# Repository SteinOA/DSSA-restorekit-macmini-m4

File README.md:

# DSSA – Mac mini M4 gjenopprettet fra Windows

**Vellykket gjenoppretting uten en ekstra Mac.** Dette repoet dokumenterer hvordan en Mac mini M4 (2024, Mac16,10) med en ny, tom 2 TB SSD ble gjenopprettet fra en Windows x64-PC. Mac-en startet deretter i macOS-oppsettsassistenten, og oppstarten ble bekreftet med bilder.

Forsøk 9 fullførte gjenopprettingen av macOS 15.6.1 (24G90) med avslutningskode 0. Her er kildekoden, de lokale rettelsene og resultatene fra arbeidet samlet.

Resultatet gjelder den konkrete maskinen og programversjonen som ble brukt. Den arkiverte programversjonen er låst til denne enhetens identitet; andre Mac-maskiner er ikke verifisert av DSSA. Arkivet inneholder enhetsspesifikke opplysninger fra forsøket.

**Sikkerhetsgjennomgang gjenstår:** Skanningene fant kjente sårbarhetsvarsler i avhengigheter. Se [faktiske resultater og gjenstående arbeid](docs/SECURITY-REVIEW-2026-10-25.md) før en ny brukerpakke bygges eller deles.

## Slik ble det gjort

Se [den tekniske fremgangsmåten](docs/FREMGANGSMATE.md) for forberedelser, bygging, maskintilpasning, driveroppsett, DFU, overvåket gjenoppretting og opprydding.

For videre arbeid på en utgave som velger målmaskin per kjøring, se også [DSSA-Mac-mini-M4-Restore](https://github.com/SteinOA/DSSA-Mac-mini-M4-Restore). Det repoet inneholder den generaliserte utviklingsutgaven; dette arkivet dokumenterer det fysisk vellykkede forsøket.

## Før Mac-en åpnes: sikkerhetskopi, Aktiveringslås og sletting

**Denne fremgangsmåten er beregnet på å gjenopprette macOS til en tom erstatnings-SSD. Den bevarer ikke data og er ikke et klone- eller dataredningsverktøy. En full DFU-gjenoppretting sletter alle data på SSD-en som er installert i mål-Mac-en. Hvis den gamle SSD-en er installert som mål, slettes også dataene på den. Ta og kontroller sikkerhetskopi før du slår av maskinen og bytter SSD.**

[Leverandørens bruksanvisning](https://expandmacmini.com/pages/diy-guide) advarer om at prosedyren sletter alle data på Mac mini, og at data på den opprinnelige SSD-en vil være utilgjengelige etter byttet og fullført gjenoppretting. Ikke regn med å sette inn den gamle SSD-en igjen som sikkerhetskopi eller for å finne Apple-kontoen etterpå.

Før maskinen åpnes, ber leverandøren eieren kontrollere den nøyaktige e-postadressen til Apple-kontoen og logge ut i Systeminnstillinger. Kontroller selv at du kan logge inn på kontoen. Ikke del passord eller legg dem i repoet.

[Apple forklarer Aktiveringslås og hvordan den slås av](https://support.apple.com/en-ie/102541): Slå av Finn Mac under Systeminnstillinger → navnet ditt → iCloud → Se alle → Finn Mac, og godkjenn selv når du blir bedt om det. Aktiveringslås er noe annet enn FileVault-diskkryptering. Den lenkede leverandørveiledningen sier ikke at FileVault må slås av. SSD-bytte og dette programmet kan ikke omgå Aktiveringslås.

Gjør disse kontrollene før avslåing og demontering.

Se [resultatet](docs/FORSOK9-RESULTAT.txt) og [kontrollpunktene](results/attempt9-restore-result.json). Den konkrete native Windows-portfeilen er rettet og testet før det vellykkede forsøket; [rettelsen er dokumentert her](docs/NATIVE-PORT-RETTELSE.txt).

Etter det vellykkede forsøket ble den midlertidige driverpakken, sertifikattilliten og den private nøkkelen fjernet. Apples drivere og tjeneste ble beholdt, og Windows-beskyttelsen var på. Detaljene er bevart i [arbeidsnotatet fra forsøket](docs/FORTSETT-HER-I-KVELD.txt).

## Innhold i repoet

- `source/`: komplett kildekode fra RestoreKit v0.5.13 med lokale rettelser og innholdet i alle vendor-moduler.
- `archives/source-snapshot.zip`: samme 2 133 kildefiler med nøyaktige opprinnelige byte. Bruk dette arkivet når kontrollsummene i `source-manifest.json` skal sammenlignes; enkelte vendor-moduler har egne Git-regler for linjeskift.
- `patches/`, `provenance.json`, `source-manifest.json`: opprinnelse, endringer, lisenser og kontrollsummer.
- `bin/windows-x64/restorekit.exe`: ferdig Windows-program, SHA256 `B59206BC8E7046FF696A87DF029BD919BCD6659E06E82D11DD940F67126D2F93`.
- `ops/`: klargjorte skript for ett overvåket forsøk og etterfølgende opprydding. De er tilpasset det opprinnelige lokale oppsettet og er ikke generelle installasjonsskript for en ny kloning av repoet.
- `driver/pid1905/`: kun den avgrensede INF/CAT-pakken for siste restore-modus. CAT inneholder det eksisterende offentlige signeringssertifikatet. Ingen privat signeringsnøkkel er bevart eller lastet opp. Historisk signaturkontroll betyr ikke at sertifikatet nå er betrodd på PC-en.
- `results/`: programtesten, oppryddingsbevis og faktiske GitHub Actions-resultater.
- `history/`: eldre skript som dokumentasjon, lagret som tekst; de skal ikke kjøres.

Midlertidige drivere og sertifikattillit krever opprydding etter bruk, også ved feil. Ikke bruk den opprinnelige brede `setup-driver`-kommandoen.

Firmware (IPSW), private nøkler, innloggingsopplysninger og lokale sertifikatlagre inngår ikke i distribusjonen.

## Hva de automatiske testene viser

Identitetsparseren og regresjonstestene er testet på Ubuntu 24.04 med GCC og Clang, inkludert AddressSanitizer og UndefinedBehaviorSanitizer, og på Windows Server 2022 med MSVC. Tre separate testkjøringer bruker ulike deterministiske startverdier og tester 100 000 tilfeller med ugyldige inndata hver.

Dette er programvaretester uten tilgang til USB-enheter, drivere, sertifikatlagre, firmware eller Mac-maskinvare. De kontrollerer parserens oppførsel og minnehåndtering. Den fysiske gjenopprettingen er dokumentert separat i resultatene fra forsøk 9.

`source-provenance.json` inneholder SHA-256-kontrollsummer for den kopierte produksjonsheaderen og de opprinnelige testdataene. Testarbeidsflytene har lesetilgang (`contents: read`), en grense på ti minutter per jobb og bruker ingen repository secrets.

## Diskmåling og ønsket enkel brukerpakke

[Én måleøkt og krav til en veiledet Windows-pakke](docs/STORAGE-TEST-AND-USER-PACKAGE.md) dokumenterer 2 TB-modulen fra Expand Mac mini, resultatene for alle tre disker og testens begrensninger. En enkel nedlastbar brukerpakke med grundig veiledning er et utviklingsmål, ikke en allerede verifisert ettklikksløsning. Andre SSD-moduler er foreløpig ikke testet.

## Sikkerhet og automatiske kontroller

Se [sikkerhetspolicyen](SECURITY.md) for privat rapportering og [kontrollenes omfang og begrensninger](docs/SECURITY-CHECKS.md). Faktiske resultater ligger under [GitHub Actions](https://github.com/SteinOA/DSSA-restorekit-macmini-m4/actions). En konfigurert kontroll er ikke det samme som en bestått kontroll. Avhengighetsoppdateringer foreslås i pull requests; de flettes ikke automatisk inn i dette historiske arkivet.

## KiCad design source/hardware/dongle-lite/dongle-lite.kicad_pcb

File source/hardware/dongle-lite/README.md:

# Dongle-Lite — KiCad hardware

The USB 2.0 variant of the RecoverKit dongle: an RP2354A + FUSB302B board that
forces an Apple Silicon / T2 Mac into DFU over USB-PD, no keyboard dance
required. See [`../README.md`](../README.md) for how the dongle family works
and how the Lite compares to the [Dongle-Pro](../dongle-pro/), `./PRD.md` for
the product spec, and `./BOM-sourcing.md` for parts sourcing.

## How it works (short version)

The host plugs into J1, the target Mac into J2. A CH334F USB 2.0 hub puts two
devices on the host's bus: the RP2354A (control + CDC serial for `restorekit`)
and the target itself. The FUSB302B drives the *target* CC line with Apple's
vendor-defined USB-PD messages to flip the Mac into DFU; an AP22653 load
switch power-cycles target VBUS for clean re-enumeration; two 74AVC1T45s
break out the target's SBU debug UART at 1.2 V. Restore data flows host ↔
target straight through the hub — the MCU only triggers, never proxies.

## Status

- **Schematic:** complete, single sheet, functionally clustered, ERC 0.
- **Layout:** two builds of the same netlist:
  - `dongle-lite.kicad_pcb` — original two-sided 4-layer layout
    (`mfg-jlcpcb/`).
  - `dongle-lite-1s4l.kicad_pcb` — **single-sided** 4-layer relayout for
    JLCPCB Economic PCBA (`mfg-jlcpcb-1s4l/`, DRC report checked in). This is
    the one to order.
- **Firmware:** `../../crates/dongle-lite-fw` (Embassy, `rp235xa`). The GPIO
  map lives in the firmware source and matches `gen/board.py`.

## Clusters

One flat sheet (`dongle-lite.kicad_sch`), five functional clusters — parts
that talk to each other are drawn wired together, only cross-cluster signals
use labels:

| Cluster | Contents |
|---------|----------|
| MCU core | RP2354A (internal stacked flash — no external QSPI part), 12 MHz crystal, BOOT button, Tag-Connect J3 |
| USB-PD | FUSB302B, I²C pull-ups, target CC |
| USB hub + ports | CH334F hub, both 16-pin USB-C receptacles, ESD arrays, host CC pull-downs |
| SBU serial | 2× 74AVC1T45 1.2 V level translators |
| Power | 3.3 V + 1.2 V LDOs, target-VBUS load switch, LEDs |

USB D+/D− pairs are impedance-controlled differential pairs on the PCB.

## How this was built

Every part is a real LCSC component. Symbols, footprints, and 3D models were
pulled with [`easyeda2kicad`](https://github.com/uPesy/easyeda2kicad.py) into
the project-local libraries under `lib/` (shared with the Pro via its `lib`
symlink); `sym-lib-table` / `fp-lib-table` register them via `${KIPRJMOD}`.

The schematic is generated, not hand-drawn: `gen/board.py` is the
authoritative netlist (every part → cluster placement, every pin → net) and
`gen/gen.py` emits the `.kicad_sch`. Regenerate:

```sh
cd hardware/dongle-lite
python3 gen/board.py            # writes dongle-lite.kicad_sch
kicad-cli sch erc dongle-lite.kicad_sch
```

## Key parts (all LCSC)

| Ref | Part | LCSC | Function |
|-----|------|------|----------|
| U1 | RP2354A | C41378174 | MCU (USB-native composite; 2 MB internal flash) |
| U2 | FUSB302BMPX | C132291 | USB-PD PHY, drives target CC (Apple DFU VDM) |
| U3 | CH334F | C5187527 | USB 2.0 hub — host sees MCU + target. `PSELF` (18) and `RESET#/CDP` (16) are left **open** — see below |
| U5 | RT9013-33GB | C47773 | 3.3 V LDO from host 5 V |
| U6 | TLV70212 | C81462 | 1.2 V LDO for the SBU translator low side |
| U8, U9 | 74AVC1T45GW | C282330 | SBU1/SBU2 level translators (3.3 ↔ 1.2 V) |
| U10 | AP22653 | C2158037 | Target-VBUS load switch (current-limited) |
| D10, D11 | USBLC6-2SC6 | C7519 | ESD arrays on host / target D± |
| J1, J2 | HRO TYPE-C-31-M-12 | C165948 | Host / target USB-C (16-pin) |
| Y1, Y2 | 12 MHz 3225 | C9002 | MCU + hub crystals |

Full BOM/CPL for ordering are in the `mfg-jlcpcb*/` packages.

### Hub strap pins

`PSELF` (18) and `RESET#/CDP` (16) on U3 are both left open, matching Adafruit's
CH334F breakout (product 5997).

`PSELF` has a built-in pull-up and defaults high = **self-powered**, which is
what makes the hub advertise 500 mA per downstream port. Tied to GND it
advertises bus-powered and caps every port at one unit load, 100 mA. A target
Mac in DFU fits under that, but every later restore stage asks for 500 mA, so
the host refuses to configure the target and the restore dies partway through
with a power error. The board still draws from the host's VBUS — this is a
declaration, not a supply.

`RESET#/CDP` is sampled at power-up too: held high it enables CDP (downstream
charging-port advertisement) and turns off the hub's low-power sleep. The
datasheet wants it "completely suspended when not reset", so there is no
pull-up on it.

## ERC configuration

`pin_not_driven`, `pin_to_pin`, `lib_symbol_issues`, and `lib_symbol_mismatch`
are set to *ignore* in the project files: the LCSC-generated symbols type
passive/IO pins as "Input/Unspecified", not real disconnections. Everything
else keeps default severity.

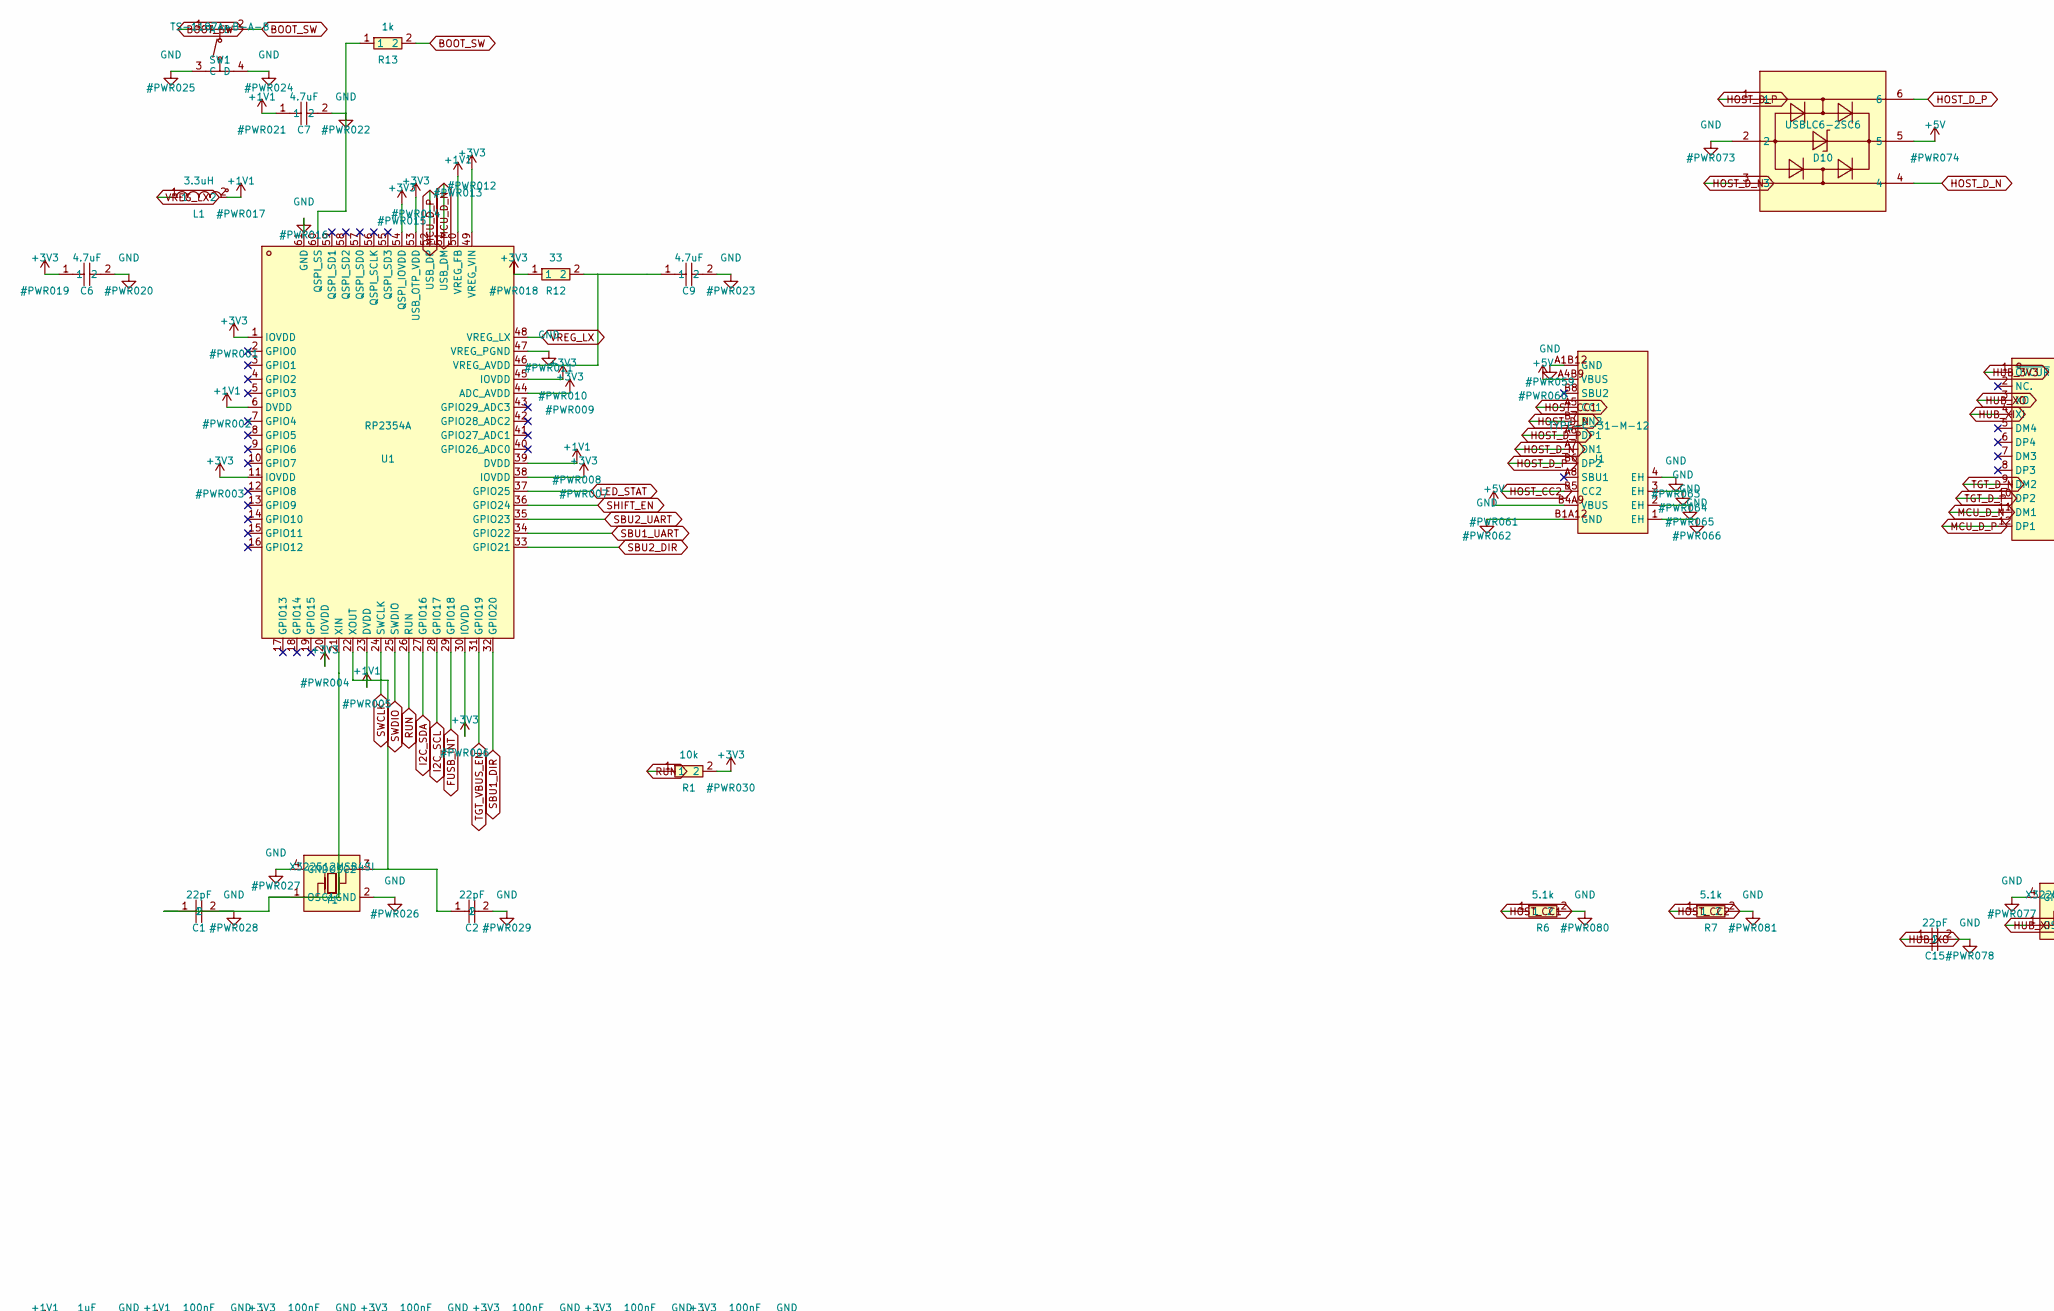
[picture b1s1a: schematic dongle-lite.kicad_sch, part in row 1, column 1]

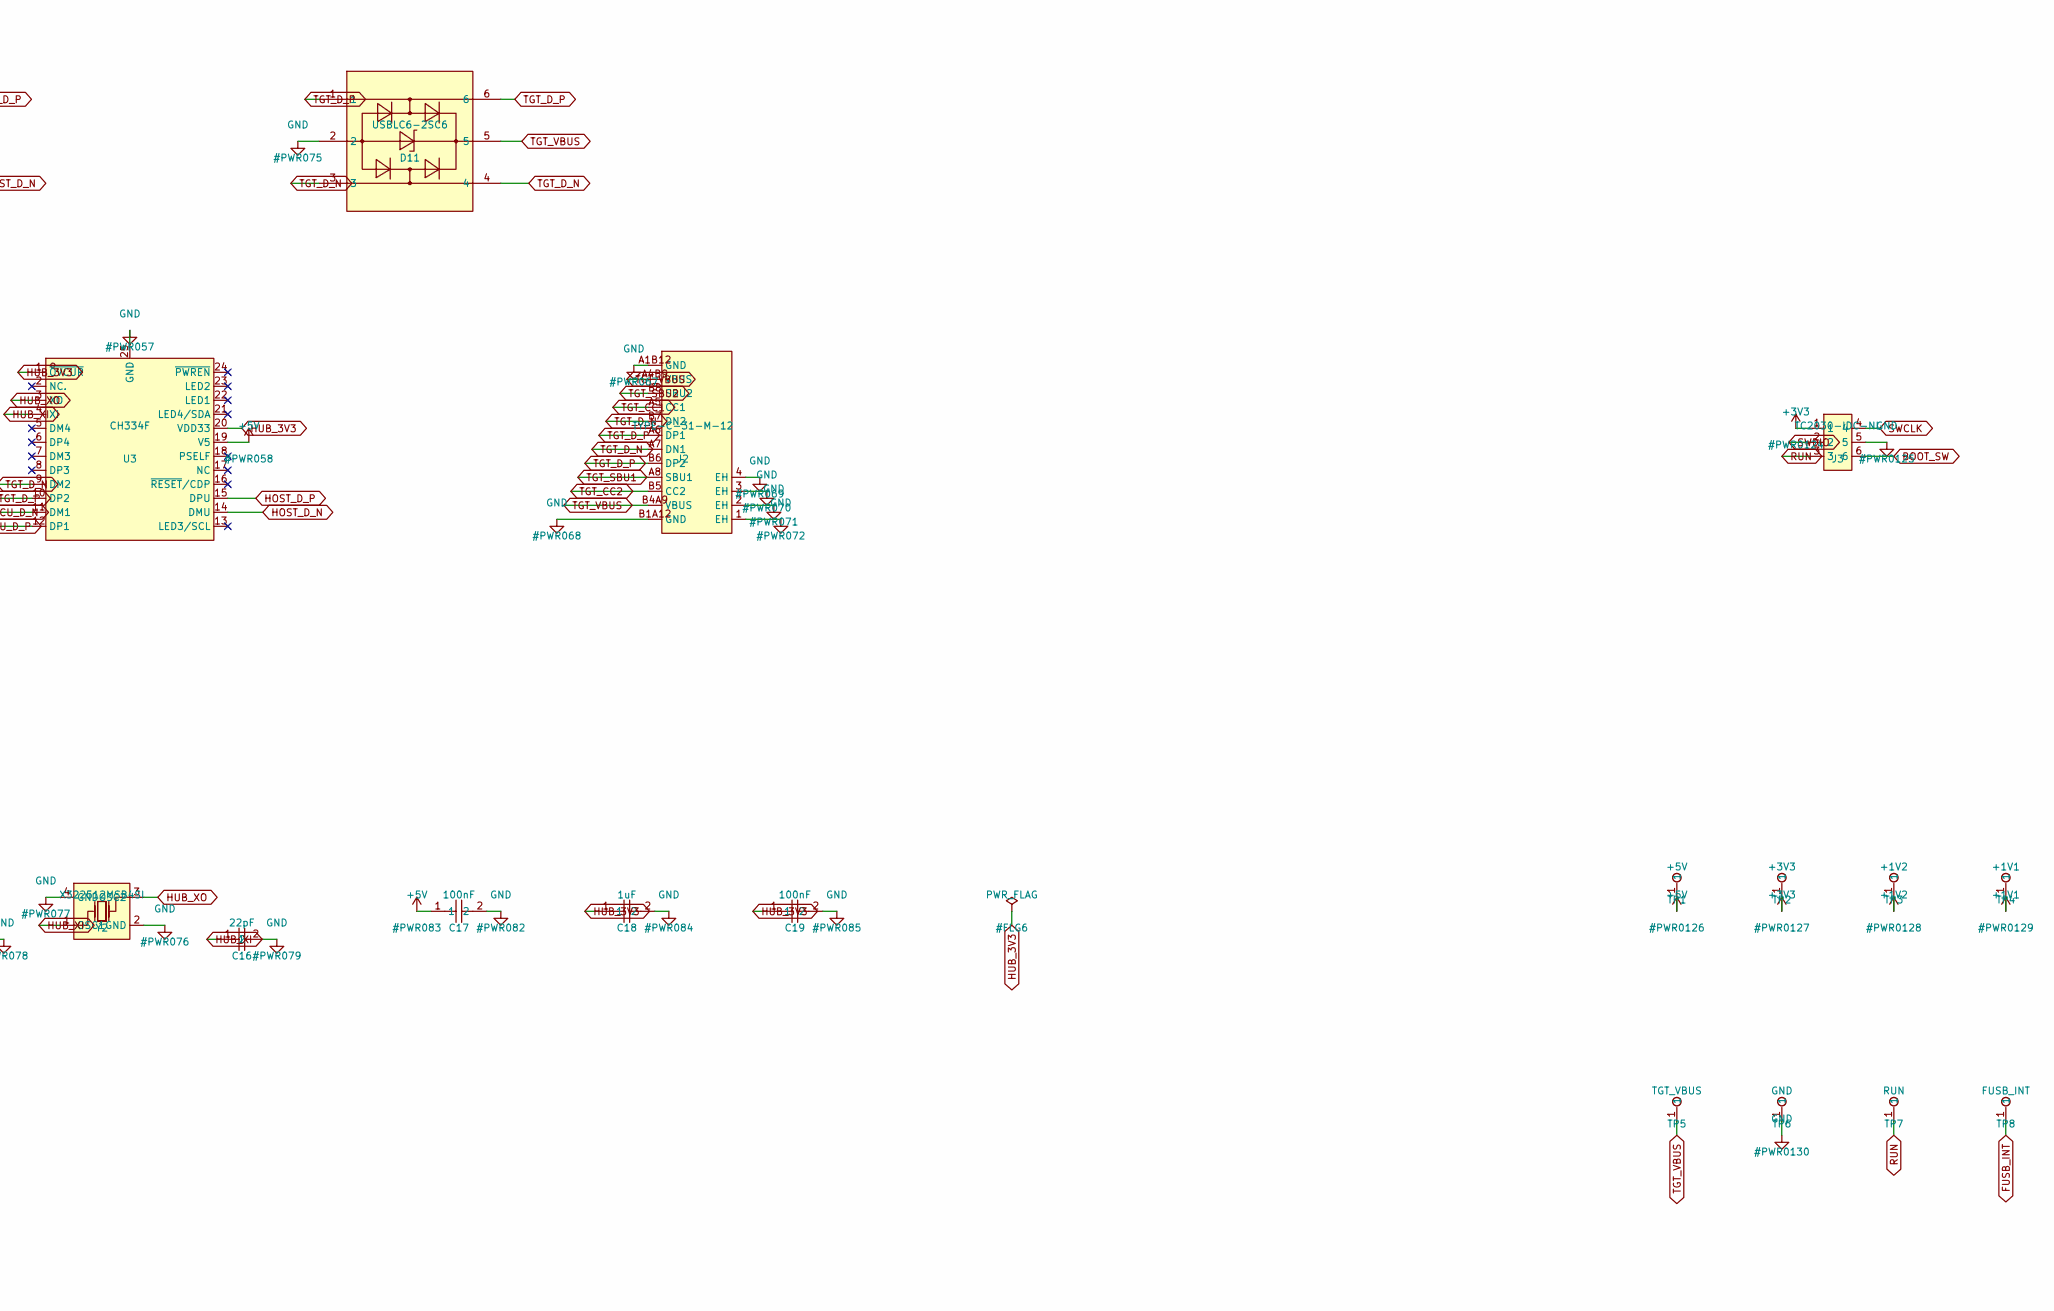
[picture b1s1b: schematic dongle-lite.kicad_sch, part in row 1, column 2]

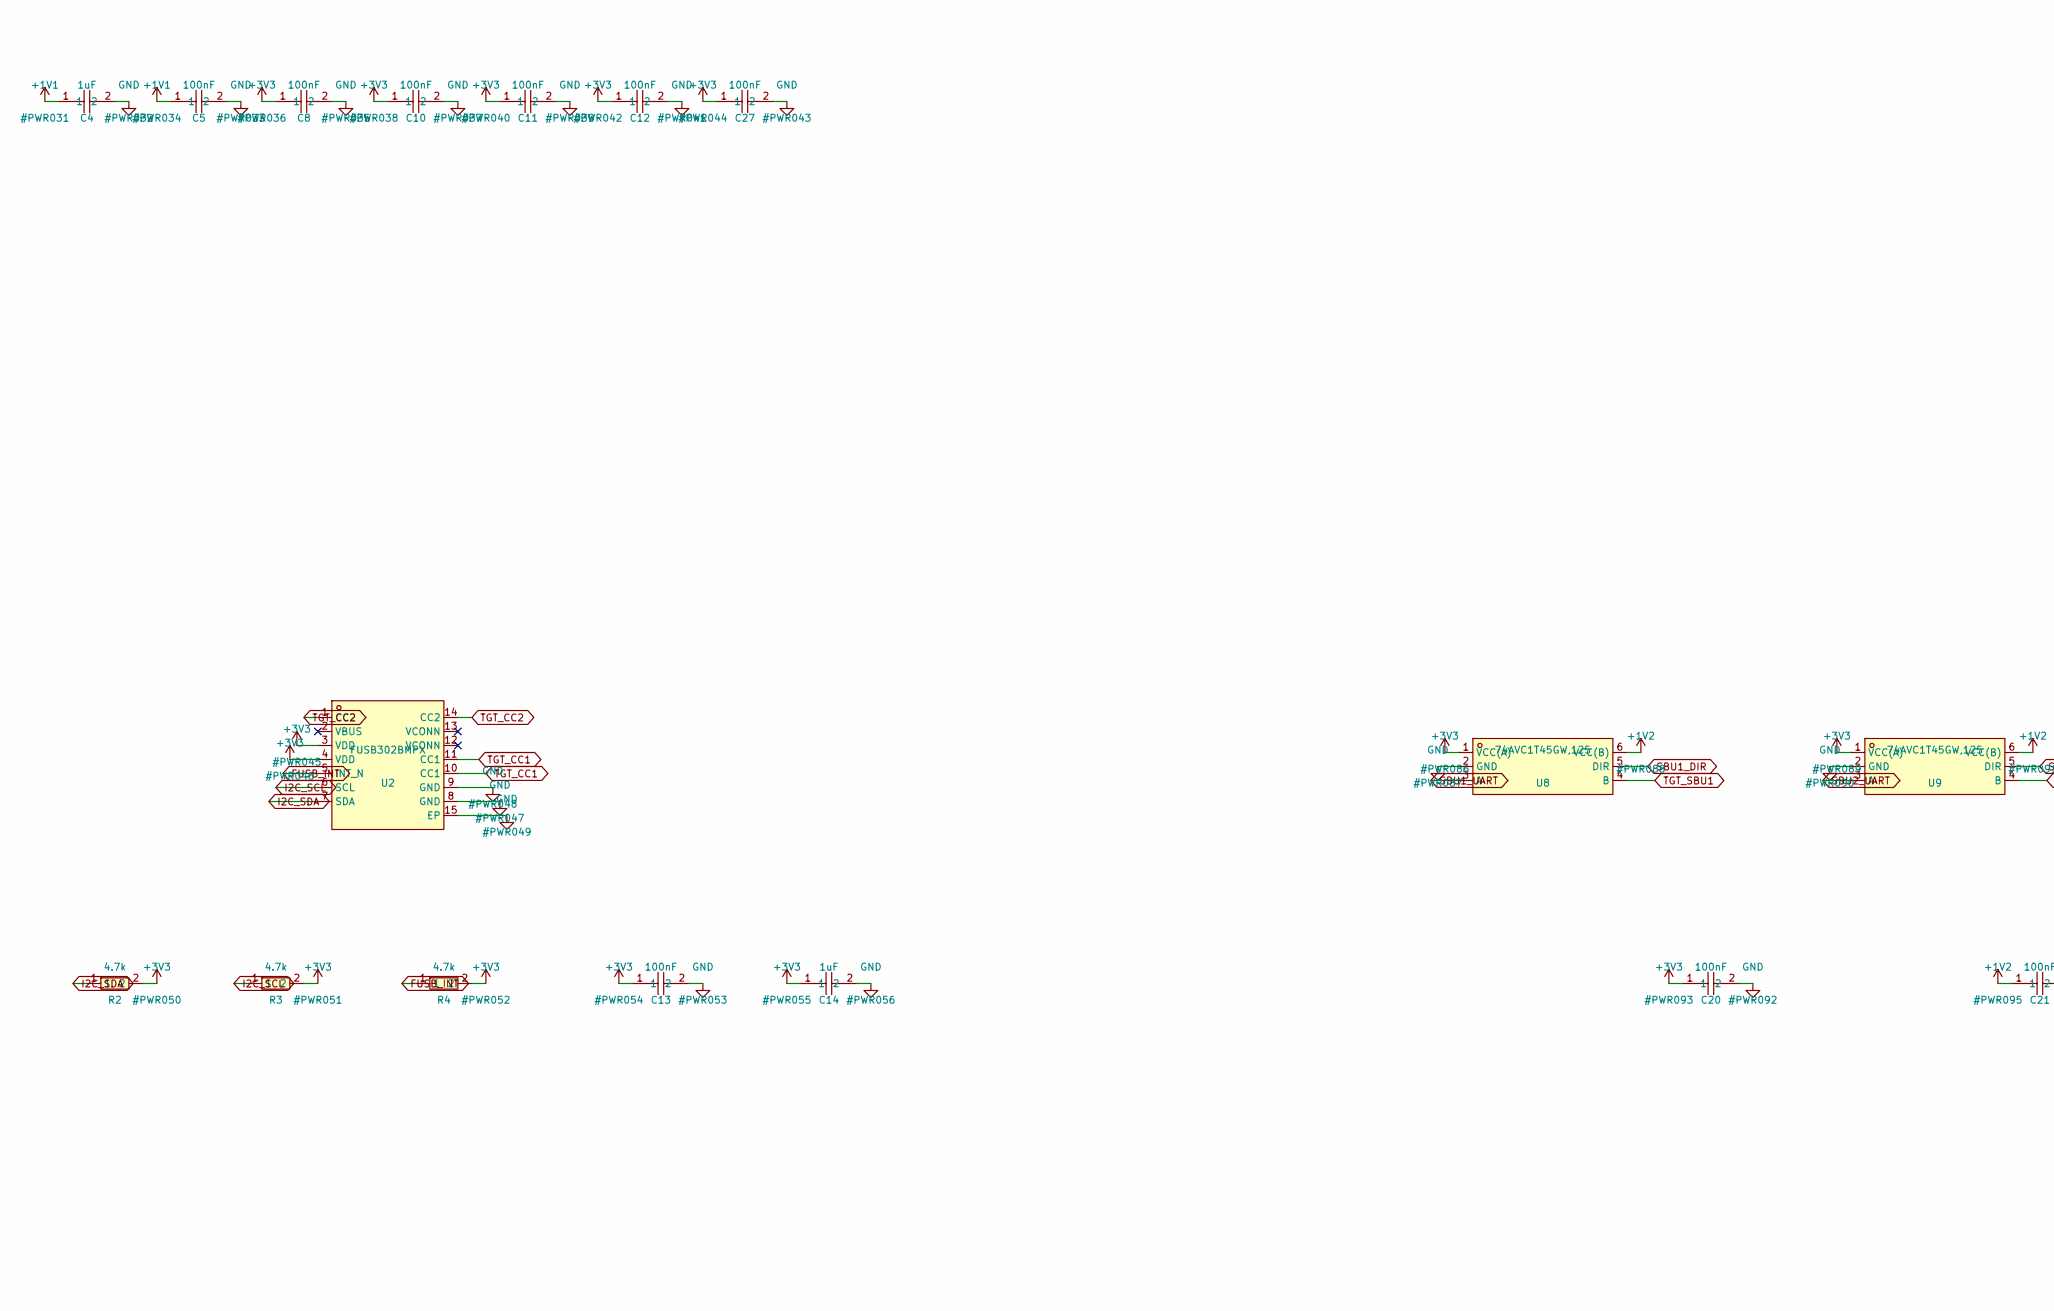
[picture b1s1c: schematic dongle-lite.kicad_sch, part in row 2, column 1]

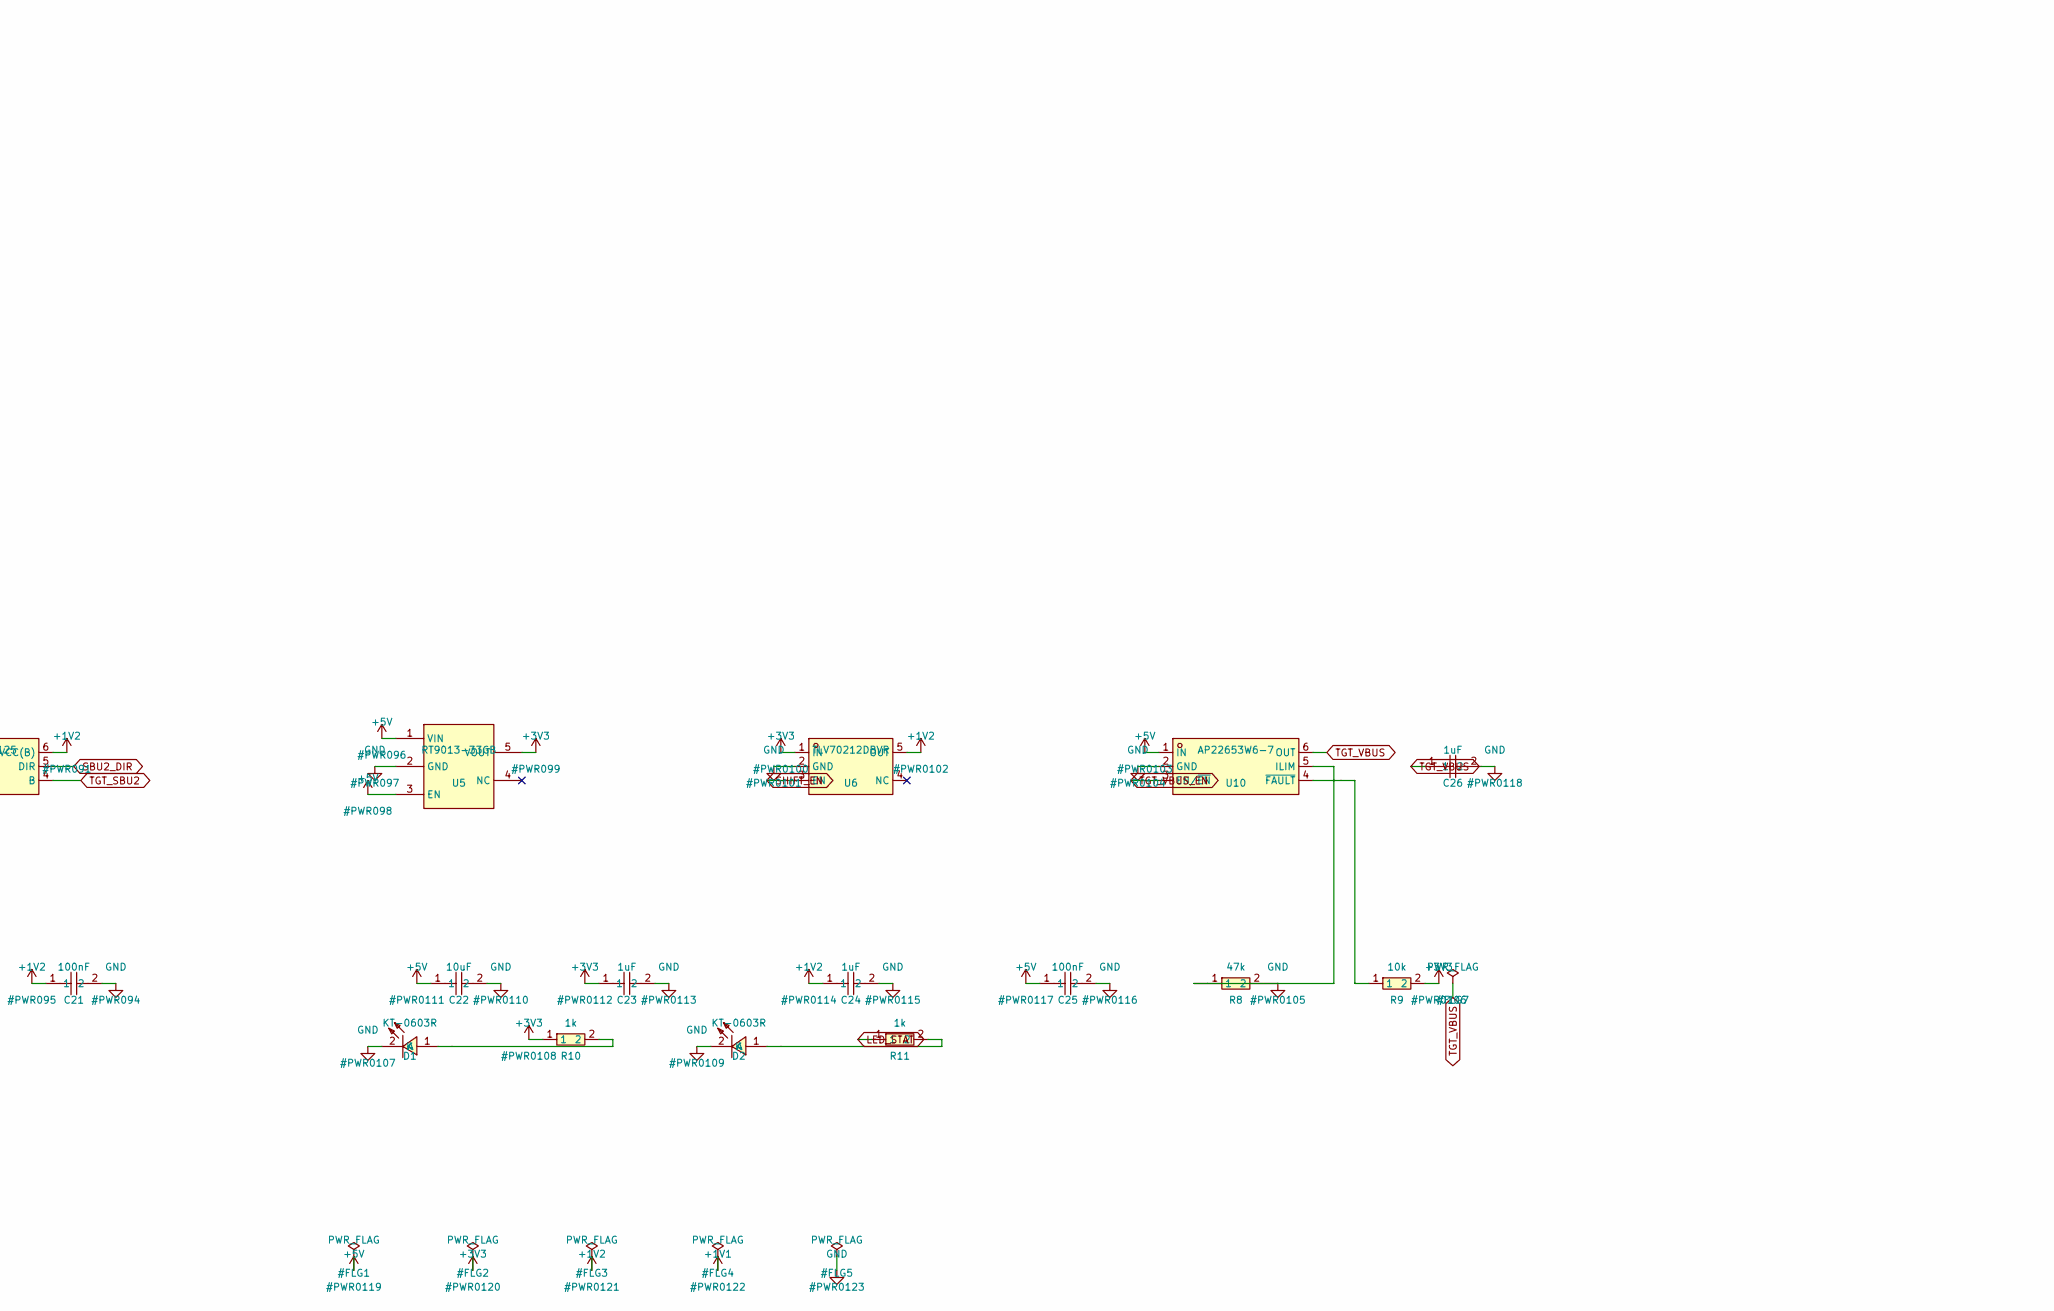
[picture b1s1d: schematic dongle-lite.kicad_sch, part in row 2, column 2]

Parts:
C1, C2, C15, C16: 22pF; C0805; LCSC C1804
C4, C14, C18, C23, C24, C26: 1uF; C0402; LCSC C52923
C5, C8, C10, C11, C12, C13, C17, C19, C20, C21, C25, C27: 100nF; C0402; LCSC C1525
C6, C7, C9: 4.7uF; C0402; LCSC C368809
C22: 10uF; C0805; LCSC C15850
D1, D2: KT-0603R; LED-SMD_L1.6-W0.8-R-RD; LCSC C2286
D10, D11: USBLC6-2SC6; SOT-23-6_L2.9-W1.6-P0.95-LS2.8-BL; LCSC C7519
J1, J2: TYPE-C-31-M-12; USB-C_SMD-TYPE-C-31-M-12_1; LCSC C165948
J3: TC2030-IDC-NL; Tag-Connect_TC2030-IDC-NL_2x03_P1.27mm_Vertical
L1: 3.3uH; IND-SMD_L2.0-W1.6_AOTA-B201610S3R3-101-T; LCSC C42411119
R1, R9: 10k; R0402; LCSC C25744
R2, R3, R4: 4.7k; R0402; LCSC C25900
R6, R7: 5.1k; R0402; LCSC C25905
R8: 47k; R0603; LCSC C25819
R10, R11, R13: 1k; R0402; LCSC C11702
R12: 33; R0402; LCSC C25105
SW1: TS-1187A-B-A-B; SW-SMD_4P-L5.1-W5.1-P3.70-LS6.5-TL_H1.5; LCSC C318884
TP1: +5V; TestPoint_Pad_D1.0mm
TP2: +3V3; TestPoint_Pad_D1.0mm
TP3: +1V2; TestPoint_Pad_D1.0mm
TP4: +1V1; TestPoint_Pad_D1.0mm
TP5: TGT_VBUS; TestPoint_Pad_D1.0mm
TP6: GND; TestPoint_Pad_D1.0mm
TP7: RUN; TestPoint_Pad_D1.0mm
TP8: FUSB_INT; TestPoint_Pad_D1.0mm
U1: RP2354A; QFN-60_L7.0-W7.0-P0.40-TL-EP3.4; LCSC C41378174
U2: FUSB302BMPX; MLP-14_L2.5-W2.5-P0.50-BL-EP; LCSC C132291
U3: CH334F; QFN-24_L4.0-W4.0-P0.50-BL-EP2.8; LCSC C5187527
U5: RT9013-33GB; SOT-23-5_L3.0-W1.7-P0.95-LS2.8-BL; LCSC C47773
U6: TLV70212DBVR; SOT-23-5_L3.0-W1.7-P0.95-LS2.8-BL; LCSC C81462
U8, U9: 74AVC1T45GW,125; SC-88-6_L2.0-W1.3-P0.65-LS2.1-BL; LCSC C282330
U10: AP22653W6-7; SOT-23-6_L2.9-W1.6-P0.95-LS2.8-BR; LCSC C2158037
Y1, Y2: X322512MSB4SI; CRYSTAL-SMD_4P-L3.2-W2.5-BL; LCSC C9002

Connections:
+1V1: C4.1, C5.1, C7.1, L1.2, TP4.1 (1_1), U1.6 (DVDD), U1.23 (DVDD), U1.39 (DVDD), U1.50 (VREG_FB)
+1V2: C21.1, C24.1, TP3.1, U6.5 (OUT), U8.6 (VCC(B)), U9.6 (VCC(B))
+3V3: C6.1, C8.1, C10.1, C11.1, C12.1, C13.1, C14.1, C20.1, C23.1, C27.1, J3.1, R1.2, R2.2, R3.2, R4.2, R9.2, R10.1, R12.1, TP2.1, U1.1 (IOVDD), U1.11 (IOVDD), U1.20 (IOVDD), U1.30 (IOVDD), U1.38 (IOVDD), U1.44 (ADC_AVDD), U1.45 (IOVDD), U1.49 (VREG_VIN), U1.53 (USB_OTP_VDD), U1.54 (QSPI_IOVDD), U2.3 (VDD), U2.4 (VDD), U5.5 (VOUT), U6.1 (IN), U8.1 (VCC(A)), U9.1 (VCC(A))
+5V: C17.1, C22.1, C25.1, D10.5, J1.A4B9 (VBUS), J1.B4A9 (VBUS), TP1.1 (1_1), U3.19 (V5), U5.1 (VIN), U5.3 (EN), U10.1 (IN)
FUSB_INT: R4.1, TP8.1, U1.29 (GPIO18), U2.5 (INT_N)
HOST_CC1: J1.A5 (CC1), R6.1
HOST_CC2: J1.B5 (CC2), R7.1
HOST_D_N: D10.3, D10.4, J1.A7 (DN1), J1.B7 (DN2), U3.14 (DMU)
HOST_D_P: D10.1, D10.6, J1.A6 (DP1), J1.B6 (DP2), U3.15 (DPU)
HUB_3V3: C18.1, C19.1, U3.1 (~OVCUR), U3.20 (VDD33)
HUB_XI: C16.1, U3.4 (XI), Y2.1 (OSC1)
HUB_XO: C15.1, U3.3 (XO), Y2.3 (OSC2)
I2C_SCL: R3.1, U1.28 (GPIO17), U2.6 (SCL)
I2C_SDA: R2.1, U1.27 (GPIO16), U2.7 (SDA)
LED_STAT: R11.1, U1.37 (GPIO25)
MCU_D_N: U1.51 (USB_DM), U3.11 (DM1)
MCU_D_P: U1.52 (USB_DP), U3.12 (DP1)
unnamed: D1.1 (A), R10.2
unnamed: D2.1 (A), R11.2
unnamed: J3.6, R13.2, SW1.1 (A), SW1.2 (B)
unnamed: C9.1, R12.2, U1.46 (VREG_AVDD)
unnamed: C2.1, U1.22 (XOUT), Y1.3 (OSC2)
unnamed: R9.1, U10.4 (~FAULT)
RUN: J3.3, R1.1, TP7.1 (1_1), U1.26 (RUN)
SBU1_DIR: U1.32 (GPIO20), U8.5 (DIR)
SBU1_UART: U1.34 (GPIO22), U8.3 (A)
SBU2_DIR: U1.33 (GPIO21), U9.5 (DIR)
SBU2_UART: U1.35 (GPIO23), U9.3 (A)
SHIFT_EN: U1.36 (GPIO24), U6.3 (EN)
SWCLK: J3.4, U1.24 (SWCLK)
SWDIO: J3.2, U1.25 (SWDIO)
TGT_CC1: J2.A5 (CC1), U2.10 (CC1), U2.11 (CC1)
TGT_CC2: J2.B5 (CC2), U2.1 (CC2), U2.14 (CC2)
TGT_D_N: D11.3, D11.4, J2.A7 (DN1), J2.B7 (DN2), U3.9 (DM2)
TGT_D_P: D11.1, D11.6, J2.A6 (DP1), J2.B6 (DP2), U3.10 (DP2)
TGT_SBU1: J2.A8 (SBU1), U8.4 (B)
TGT_SBU2: J2.B8 (SBU2), U9.4 (B)
TGT_VBUS: C26.1, D11.5, J2.A4B9 (VBUS), J2.B4A9 (VBUS), TP5.1 (1_1), U10.6 (OUT)
TGT_VBUS_EN: U1.31 (GPIO19), U10.3 (EN/~EN)
VREG_LX: L1.1, U1.48 (VREG_LX)

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
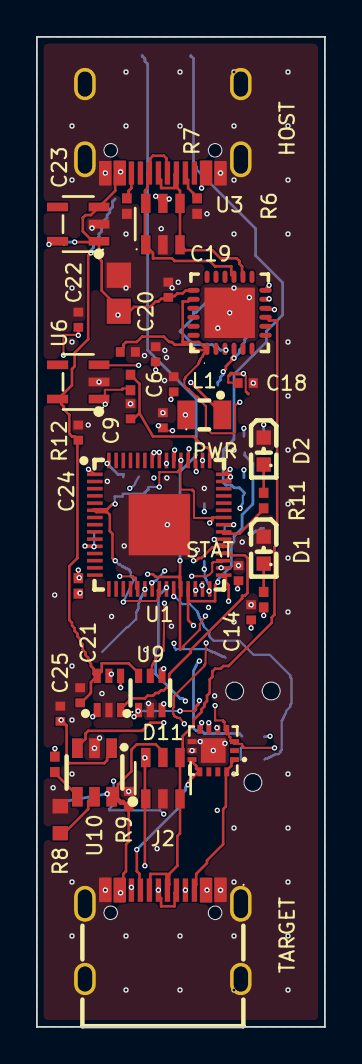
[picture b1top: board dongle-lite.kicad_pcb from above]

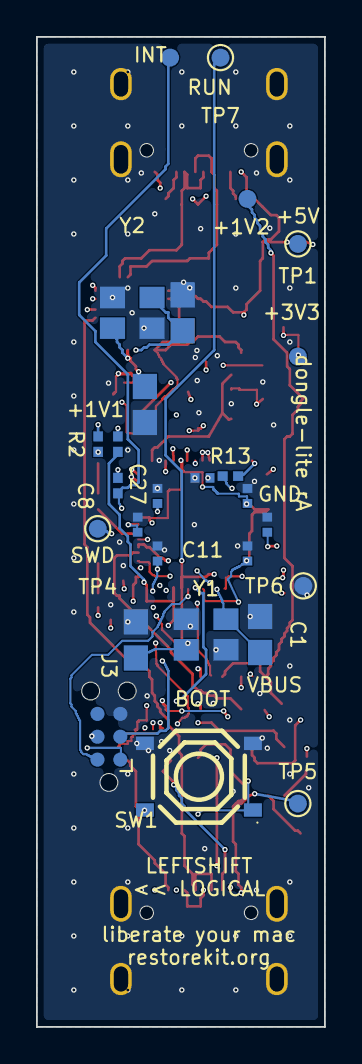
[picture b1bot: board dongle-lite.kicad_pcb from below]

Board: 6 copper layers, 16.0 x 55.0 mm, 65 parts (27 on the bottom side), 44 nets.

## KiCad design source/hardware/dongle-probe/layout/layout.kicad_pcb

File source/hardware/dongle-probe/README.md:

# dongle-probe

SWD probe for flashing dongle-lite and dongle-pro boards over their TC2030 pads.
The TC2030-IDC-NL cable plugs straight into J2, no adapter wiring.

RP2354A + USB-C, runs the stock [debugprobe](https://github.com/raspberrypi/debugprobe)
firmware built for Pico 2 (`DEBUG_ON_PICO=ON`): GP2 = SWCLK, GP3 = SWDIO, GP25 = activity
LED. Hold BOOT while plugging in and drop the UF2 on the mass storage device.

J2 is a shrouded 2.54 mm 2x3 box header; the TC2030-IDC-NL cable ends in a
6-pin 0.1" IDC socket whose polarizing bump only fits the key notch one way.
It's wired 1:1 with the target TC2030 pads:

| Pin | Signal |
|-----|--------|
| 1 | VTREF (bridge JP1 to power the target at 3.3V) |
| 2 | SWDIO |
| 3 | nRESET (GP6, unused by stock firmware) |
| 4 | SWCLK |
| 5 | GND |
| 6 | BOOT (GP7, unused by stock firmware) |

Pin 6 pairs with dongle boards that route their TC2030 pin 6 to the BOOTSEL
net: hold GP7 low, pulse GP6, and the target wakes up in USB boot mode.
Boards with pin 6 unrouted just ignore it.

Designed with [pcb](https://github.com/diodeinc/pcb). Schematic source is
`dongle-probe.zen` plus `components/`, symbols and footprints reused from
dongle-lite in `lib/`.

```sh
pcb build              # validate
pcb layout dongle-probe.zen   # regenerate layout/ and open KiCad
```

The routed board lives in `layout/layout.kicad_pcb` (don't re-run
`pcb layout` unless you want to re-place and re-route from scratch). The
`gen_*.py` scripts are KiCad-python helpers that were used to place and
route it; they need KiCad's bundled interpreter:

```sh
/Applications/KiCad/KiCad.app/Contents/Frameworks/Python.framework/Versions/3.9/bin/python3 gen_place.py
```

## Manufacturing

`mfg-jlcpcb/` has the full JLCPCB package: gerber zip, `bom.csv`,
`cpl.csv` (all LCSC parts), and `README-JLCPCB.md` with ordering notes.

## Case

`case/` has a snap-fit printed enclosure (CadQuery, `uv run case.py`).

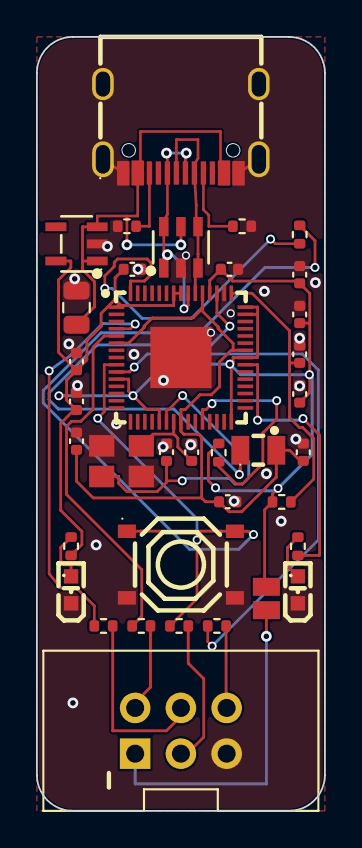
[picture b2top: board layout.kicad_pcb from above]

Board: 2 copper layers, 16.0 x 43.0 mm, 36 parts (0 on the bottom side), 27 nets.

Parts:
C1: GRM21BZ71E106KE15K; C_0805_2012Metric
C2, C8: GRM155Z71A105KE01D; C_0402_1005Metric
C3, C4, C5: 4.7uF; C_0402_1005Metric
C6, C7: GCM1555C1H220FA16D; C_0402_1005Metric
C9, C10, C11, C12, C13, C14: GCM155R71H104KE02D; C_0402_1005Metric
D1, D2: KT-0603R; LED-SMD_L1.6-W0.8-R-RD
D3: USBLC6-2SC6; SOT-23-6_L2.9-W1.6-P0.95-LS2.8-BL
J1: TYPE-C-31-M-12; USB-C_SMD-TYPE-C-31-M-12_1
J2: 2.54-2*3P; PinHeader_2x03_P1.27mm_Vertical
JP1: SolderJumper-2_P1.3mm_Open_Pad1.0x1.5mm
L1: AOTA-B201610S3R3-101-T; IND-SMD_L2.0-W1.6_AOTA-B201610S3R3-101-T
R1, R2, R4: ERJ-2RKF5101X; R_0402_1005Metric
R3, R6, R7, R8, R11: ERJ-2RKF33R0X; R_0402_1005Metric
R5, R9, R10: ERJ-2RKF1001X; R_0402_1005Metric
SW1: TS-1187A-B-A-B; SW-SMD_4P-L5.1-W5.1-P3.70-LS6.5-TL_H1.5
U1: RP2354A; QFN-60_L7.0-W7.0-P0.40-TL-EP3.4
U2: RT9013-33GB; SOT-23-5_L3.0-W1.7-P0.95-LS2.8-BL
Y1: X322512MSB4SI; CRYSTAL-SMD_4P-L3.2-W2.5-BL

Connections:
+1V1: C4.1, C8.1, C9.1, L1.2, U1.6, U1.23, U1.39, U1.50
+3V3: C2.1, C3.1, C10.1, C11.1, C12.1, C13.1, C14.1, JP1.1, R3.1, R4.2, R9.1, U1.1, U1.11, U1.20, U1.30, U1.38, U1.44, U1.45, U1.49, U1.53, U1.54, U2.5
BOOT_SW: R5.2, SW1.1, SW1.2
CC1: J1.A5, R1.1
CC2: J1.B5, R2.1
GND: C1.2, C2.2, C3.2, C4.2, C5.2, C6.2, C7.2, C8.2, C9.2, C10.2, C11.2, C12.2, C13.2, C14.2, D1.2, D2.2, D3.2, J1.1, J1.2, J1.3, J1.4, J1.A1B12, J1.B1A12, J2.5, R1.2, R2.2, SW1.3, SW1.4, U1.47, U1.61, U2.2, Y1.2, Y1.4
LEDA_A: D2.1, R10.2
LEDP_A: D1.1, R9.2
LED_ACT: R10.1, U1.37
PROBE_BOOT: R11.1, U1.10
PROBE_RESET: R8.1, U1.9
PROBE_SWCLK: R6.1, U1.4
PROBE_SWDIO: R7.1, U1.5
QSPI_SS: R5.1, U1.60
RUN: R4.1, U1.26
TGT_BOOT: J2.6, R11.2
TGT_RESET: J2.3, R8.2
TGT_SWCLK: J2.4, R6.2
TGT_SWDIO: J2.2, R7.2
TGT_VTREF: J2.1, JP1.2
USB_DM: D3.3, D3.4, J1.A7, J1.B7, U1.51
USB_DP: D3.1, D3.6, J1.A6, J1.B6, U1.52
VBUS: C1.1, D3.5, J1.A4B9, J1.B4A9, U2.1, U2.3
VREG_AVDD: C5.1, R3.2, U1.46
VREG_LX: L1.1, U1.48
XIN: C6.1, U1.21, Y1.1
XOUT: C7.1, U1.22, Y1.3

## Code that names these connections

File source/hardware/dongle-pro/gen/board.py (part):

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def c(ref,val,at,a,b): add(ref,C[val],at,{"1":a,"2":b},val)

# ===== MCU core cluster — RP2354A (RP2350 die + 2MB internal flash) =====
# GPIO map for firmware:  GP16=I2C_SDA GP17=I2C_SCL GP18=FUSB_INT GP19=TGT_VBUS_EN
#   GP20=SBU1_DIR GP21=SBU2_DIR GP22=SBU1_UART GP23=SBU2_UART GP24=SHIFT_EN GP25=LED_STAT
#   GP26=SS_SEL (HD3SS3212 lane select, H=CC2/flipped)  GP27=HUB_RSTn (GL3510 reset, drive low to reset)
add("U1","RP2354A_C41378174",(150,150,0),{
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gen.build_wired(comps,"dongle-pro.kicad_sch",
                {"GND":"GND","+3V3":"+3V3","+1V2":"+1V2","+5V":"+5V","+1V1":"+1V1"},
                wires=[], auto_wire_dist=90, paper="A0", project="dongle-pro",
                force_label=SS_PAIRS|{"HOST_D_P","HOST_D_N","TGT_D_P","TGT_D_N","MCU_D_P","MCU_D_N"})
print(f"{len(comps)} comps")

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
